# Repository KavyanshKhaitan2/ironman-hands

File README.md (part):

# Ironman-Hands!
[View in OnShape](https://cad.onshape.com/documents/6b24d13ccce8b20dadd52a3a/w/196c8f17dbb1cb6e287c322c/e/852bd395ec118001130bafdd?renderMode=0&uiState=6a15cbbf1f6b6ce009f7e8d0)

A glove which you can wear and control your computer by moving your hand and using gestures!! (It has a lot of sensors to do this!)

I will be stitching all the parts together on a glove, and then adding some more cloth on top so no exposed wires or PCBs are visible!

## Contents
Quickly jump to different parts of the README using this section!
1. [Why?](#why)
1. [Fallout Zine](#fallout-zine)
2. [PCB](#pcb)
3. [Schematics](#schematics)
4. [Case](#case)
5. [Bill of Materials](#bom)
6. [Assembly](#assembly)
## Why?
I watched the Iron Man Movie, and it was always fascinating to me how he controlled the screen using just his hands, so I decided to build to make that true and real!

## Fallout Zine
[Jump to Contents](#contents)

<image height="400" src="https://github.com/KavyanshKhaitan2/ironman-hands/blob/main/zine/Zine_PNG.png?raw=true">

- [ [Download JPEG file](https://github.com/KavyanshKhaitan2/ironman-hands/blob/main/zine/Zine_JPEG.jpg) ]
- [ [Download PNG file](https://github.com/KavyanshKhaitan2/ironman-hands/blob/main/zine/Zine_PNG.png) ]
- [ [Download High-Res PNG file](https://github.com/KavyanshKhaitan2/ironman-hands/blob/main/zine/Zine_PNG_HighRes.png) ]
- [ [Download Digital RGB PDF file](https://github.com/KavyanshKhaitan2/ironman-hands/blob/main/zine/Zine_Digital_RGB.pdf) ]
- [ [Download Print CMYK PDF file](https://github.com/KavyanshKhaitan2/ironman-hands/blob/main/zine/Zine_Print_CMYK.pdf) ]

[Jump to Contents](#contents)

## PCB
[Jump to Contents](#contents)

- [Mainboard](#mainboard)
- [Finger module](#finger-module)
- [BackLEDs](#backleds)
- [Power module](#power-module)

### Mainboard

- [ [Open in KiCanvas](https://kicanvas.org/?repo=https%3A%2F%2Fgithub.com%2FKavyanshKhaitan2%2Fironman-hands%2Fblob%2Fmain%2Fpcb%2Fmainboard.kicad_pcb) ]

[Jump to Contents](#contents)

### Finger module

- [ [Open in KiCanvas](https://kicanvas.org/?repo=https%3A%2F%2Fgithub.com%2FKavyanshKhaitan2%2Fironman-hands%2Fblob%2Fmain%2Fpcb%2Ffinger-mods.kicad_pcb) ]

[Jump to Contents](#contents)

### BackLEDs

- [ [Open in KiCanvas](https://kicanvas.org/?repo=https%3A%2F%2Fgithub.com%2FKavyanshKhaitan2%2Fironman-hands%2Fblob%2Fmain%2Fpcb%2Fbackleds.kicad_pcb) ]

[Jump to Contents](#contents)

### Power module

- [ [Open in KiCanvas](https://kicanvas.org/?repo=https%3A%2F%2Fgithub.com%2FKavyanshKhaitan2%2Fironman-hands%2Fblob%2Fmain%2Fpcb%2Fbattery_module%2Fbattery_module%2Fbattery_module.kicad_pcb) ]

[Jump to Contents](#contents)

## Schematics
[Jump to Contents](#contents)

- [Mainboard](#mainboard-1)
- [Finger module P1](#finger-module-p1)
- [Finger module P2](#finger-module-p2)
- [Power module](#power-module-1)

### Mainboard

[ [View in KiCanvas](https://kicanvas.org/?repo=https%3A%2F%2Fgithub.com%2FKavyanshKhaitan2%2Fironman-hands%2Fblob%2Fmain%2Fpcb%2Fmainboard.kicad_sch) ]

[Jump to Contents](#contents)

### Finger module P1

[ [View in KiCanvas](https://kicanvas.org/?repo=https%3A%2F%2Fgithub.com%2FKavyanshKhaitan2%2Fironman-hands%2Fblob%2Fmain%2Fpcb%2Ffinger-mods.kicad_sch) ]

[Jump to Contents](#contents)

### Finger module P2

[ [View in KiCanvas](https://kicanvas.org/?repo=https%3A%2F%2Fgithub.com%2FKavyanshKhaitan2%2Fironman-hands%2Fblob%2Fmain%2Fpcb%2Ffinger_mod_p2.kicad_sch) ]

[Jump to Contents](#contents)

### Power module

[ [View in KiCanvas](https://kicanvas.org/?repo=https%3A%2F%2Fgithub.com%2FKavyanshKhaitan2%2Fironman-hands%2Fblob%2Fmain%2Fpcb%2Fbattery_module%2Fbattery_module%2Fbattery_module.kicad_sch) ]

[Jump to Contents](#contents)

## Case
### Final assembly:

[ [View in OnShape](https://cad.onshape.com/documents/6b24d13ccce8b20dadd52a3a/w/196c8f17dbb1cb6e287c322c/e/852bd395ec118001130bafdd?renderMode=0&uiState=6a15cbbf1f6b6ce009f7e8d0) ]

[Jump to Contents](#contents)

## BOM
(Bill of Materials)

[ [View in Google Sheets](https://docs.google.com/spreadsheets/d/10JJsmnbrsMaL60rsXx-CBmIgtjZ1htyX9JACOBp3yb4/edit?usp=sharing) ]
[ [Open CSV in GitHub](https://github.com/KavyanshKhaitan2/ironman-hands/blob/main/production/BOM.csv) ]

- [Cumulative](#cumulative)
- [Mainboard](#mainboard)
- [Per-finger module](#per-finger-module)
- [Power](#power)
- [Misc](#misc)

[Jump to Contents](#contents)

### Cumulative

[Jump to Contents](#contents)

### Mainboard
<table cellspacing="0" cellpadding="0">
    <tr>
        <th>
            <div>2</div>
        </th>
        <td>PCB</td>
        <td>0.4000</td>
        <td>
            <span>USD</span>
        </td>
        <td>-</td>
        <td>5</td>
        <td>1</td>
        <td>2.00</td>
        <td>USD</td>
        <td>₹191.36</td>
        <td>$2.00</td>
    </tr>
    <tr>
        <th>
            <div>3</div>
        </th>
        <td>Header pins (90deg)</td>
        <td>0.2000</td>
        <td>
            <span>INR</span>
        </td>
        <td>
            <a href="https://quartzcomponents.com/collections/all/products/male-90-degree-pin-header-connector"
                >QuartzComponents</a
            >
        </td>
        <td>40</td>
        <td>34</td>
        <td>8.00</td>
        <td>INR</td>
        <td>₹199.36</td>
        <td>$2.08</td>
    </tr>
    <tr>
        <th>
            <div>4</div>
        </th>
        <td>TYPE-C-31-M-12</td>
        <td>0.1719</td>
        <td>
            <span>USD</span>
        </td>
        <td>
            <a href="https://www.lcsc.com/product-detail/C165948.html">LCSC</a>
        </td>
        <td>5</td>
        <td>1</td>
        <td>0.86</td>
        <td>USD</td>
        <td>₹281.60</td>
        <td>$2.94</td>
    </tr>
    <tr>
        <th>
            <div>5</div>
        </th>
        <td>LM1117MP-3.3/TR</td>
        <td>0.0931</td>
        <td>
            <span>USD</span>
        </td>
        <td>
            <a href="https://www.lcsc.com/product-detail/C498153.html">LCSC</a>
        </td>
        <td>5</td>
        <td>1</td>
        <td>0.47</td>
        <td>USD</td>
        <td>₹326.14</td>
        <td>$3.41</td>
    </tr>
    <tr>
        <th>
            <div>6</div>
        </th>
        <td>SS56 Diode</td>
        <td>0.0471</td>
        <td>
            <span>USD</span>
        </td>
        <td>
            <a href="https://www.lcsc.com/product-detail/C65009.html">LCSC</a>
        </td>
        <td>10</td>
        <td>1</td>
        <td>0.47</td>
        <td>USD</td>
        <td>₹371.21</td>
        <td>$3.88</td>
    </tr>
    <tr>
        <th>
            <div>7</div>
        </th>
        <td>ESP32-S3-WROOM-1</td>
        <td>371.0000</td>
        <td>
            <span>INR</span>
        </td>
        <td>
            <a href="https://www.etstore.in/products/a2724">ETStore</a>
        </td>
        <td>1</td>
        <td>1</td>
        <td>371.00</td>
        <td>INR</td>
        <td>₹742.21</td>
        <td>$7.76</td>
    </tr>
    <tr>
        <th>
            <div>8</div>
        </th>
        <td>LSM6DS3TR-C</td>
        <td>1.5474</td>
        <td>
            <span>USD</span>
        </td>
        <td>
            <a href="https://www.lcsc.com/product-detail/C967633.html">LCSC</a>
        </td>
        <td>1</td>
        <td>1</td>
        <td>1.55</td>
        <td>USD</td>
        <td>₹890.27</td>
        <td>$9.30</td>
    </tr>
    <tr>
        <th>
            <div>9</div>
        </th>
        <td>TCA9548APWR</td>
        <td>0.6418</td>
        <td>
            <span>USD</span>
        </td>
        <td>
            <a href="https://www.lcsc.com/product-detail/C130026.html">LCSC</a>
        </td>
        <td>1</td>
        <td>1</td>
        <td>0.64</td>
        <td>USD</td>
        <td>₹951.68</td>
        <td>$9.95</td>
    </tr>
    <tr>
        <th>
            <div>10</div>
        </th>
        <td>SK6812MINI-E</td>
        <td>0.0870</td>
        <td>
            <span>USD</span>
        </td>
        <td>
            <a href="https://www.lcsc.com/product-detail/C5149201.html">LCSC</a>
        </td>
        <td>5</td>
        <td>6</td>
        <td>0.87</td>
        <td>USD</td>
        <td>₹1,034.92</td>
        <td>$10.82</td>
    </tr>
    <tr>
        <th>
            <div>11</div>
        </th>
        <td>10k 1206 resistor</td>
        <td>0.4500</td>
        <td>
            <span>INR</span>
        </td>
        <td>
            <a
                href="https://quartzcomponents.com/collections/all/products/yageo-510k-ohm-1206-package-1-4w-smd-resistor-1-tolerance-pack-of-20-pieces"
                >QuartzComponents</a
            >
        </td>
        <td>20</td>
        <td>2</td>
        <td>9.00</td>
        <td>INR</td>
        <td>₹1,043.92</td>
        <td>$10.91</td>
    </tr>
    <tr>
        <th>
            <div>12</div>
        </th>
        <td>100nF 0805 capacitor</td>
        <td>1.5000</td>
        <td>
            <span>INR</span>
        </td>
        <td>
            <a
                href="https://quartzcomponents.com/collections/all/products/100nf-0-1uf-104-50v-1206-smd-capacitor-pack-of-10-pieces"
                >QuartzComponents</a
            >
        </td>
        <td>10</td>
        <td>2</td>
        <td>15.00</td>
        <td>INR</td>
        <td>₹1,058.92</td>
        <td>$11.07</td>
    </tr>
</table>

[Jump to Contents](#contents)

### Per-finger module
<table cellspacing="0" cellpadding="0">
    <tbody>
        <tr>
            <td>Item Name</td>
            <td>
                <div>Unit Price</div>
            </td>
            <td>
                <div>Cur.</div>
            </td>
            <td>Link</td>
            <td>
                <div>Min Qty.</div>
            </td>
            <td>
                <div>Qty.</div>
            </td>
            <td>
                <div>Amount</div>
            </td>
            <td>Co1</td>
            <td>
                <div>1.. Run. Total</div>
            </td>
            <td>
                <div>2.. Run. Total</div>
            </td>
        </tr>
        <tr>
            <td>PCB</td>
            <td>0.4000</td>
            <td>
                <span>USD</span>
            </td>
            <td>-</td>
            <td>5</td>
            <td>4</td>
            <td>2.00</td>
            <td>USD</td>
            <td>₹191.36</td>
            <td>$2.00</td>
        </tr>
        <tr>
            <td>Header pins (90deg)</td>
            <td>0.2000</td>
            <td>
                <span>INR</span>
            </td>
            <td>
                <a href="https://quartzcomponents.com/collections/all/products/male-90-degree-pin-header-connector"
                    >QuartzComponents</a
                >
            </td>
            <td>40</td>
            <td>18</td>
            <td>8.00</td>
            <td>INR</td>
            <td>₹199.36</td>
            <td>$2.08</td>
        </tr>
        <tr>
            <td>LSM6DS3TR-C</td>
            <td>1.5474</td>
            <td>
                <span>USD</span>
            </td>
            <td>
                <a href="https://www.lcsc.com/product-detail/C967633.html">LCSC</a>
            </td>
            <td>1</td>
            <td>2</td>
            <td>3.09</td>
            <td>USD</td>
            <td>₹495.48</td>
            <td>$5.18</td>
        </tr>
        <tr>
            <td>10k 1206 resistor</td>
            <td>0.4500</td>
            <td>
                <span>INR</span>
            </td>
            <td>
                <a
                    href="https://quartzcomponents.com/collections/all/products/yageo-510k-ohm-1206-package-1-4w-smd-resistor-1-tolerance-pack-of-20-pieces"
                    >QuartzComponents</a
                >
            </td>
            <td>40</td>
            <td>4</td>
            <td>18.00</td>
            <td>INR</td>
            <td>₹513.48</td>
            <td>$5.37</td>
        </tr>
        <tr>
            <td>100nF 0805 capacitor</td>
            <td>1.5000</td>
            <td>
                <span>INR</span>
            </td>
            <td>
                <a
                    href="https://quartzcomponents.com/collections/all/products/100nf-0-1uf-104-50v-1206-smd-capacitor-pack-of-10-pieces"
                    >QuartzComponents</a
                >
            </td>
            <td>30</td>
            <td>4</td>
            <td>45.00</td>
            <td>INR</td>
            <td>₹558.48</td>
            <td>$5.84</td>
        </tr>
        <tr>
            <td>SK6812MINI-E</td>
            <td>0.0870</td>
            <td>
                <span>USD</span>
            </td>
            <td>
                <a href="https://www.lcsc.com/product-detail/C5149201.html">LCSC</a>
            </td>
            <td>5</td>
            <td>2</td>
            <td>0.44</td>
            <td>USD</td>
            <td>₹600.10</td>
            <td>$6.27</td>
        </tr>
    </tbody>
</table>

[Jump to Contents](#contents)

### Power

<table cellspacing="0" cellpadding="0">
    <tr>
        <td>Item Name</td>
        <td>Unit Price</td>
        <td>Cur.</td>
        <td>Link</td>
        <td>Min Qty.</td>
        <td>Qty.</td>
        <td>Amount</td>
        <td>Co1</td>
        <td>1.. Run. Total</td>
        <td>2.. Run. Total</td>
    </tr>
    <tr>
        <td>PCB</td>
        <td>1.4000</td>
        <td>USD</td>
        <td>-</td>
        <td>5</td>
        <td>1</td>
        <td>7.00</td>
        <td>USD</td>
        <td>₹669.78</td>
        <td>$7.00</td>
    </tr>
    <tr>
        <td>Header pins (90deg)</td>
        <td>0.2000</td>
        <td>INR</td>
        <td>
            <a href="https://quartzcomponents.com/collections/all/products/male-90-degree-pin-header-connector"
                >QuartzComponents</a
            >
        </td>
        <td>40</td>
        <td>16</td>
        <td>8.00</td>
        <td>INR</td>
        <td>₹8.00</td>
        <td>$0.08</td>
    </tr>
    <tr>
        <td>DC Barrel Jack</td>
        <td>6.0000</td>
        <td>INR</td>
        <td>
            <a href="https://quartzcomponents.com/products/female-dc-power-supply-connector-barrel-dc-jack"
                >QuartzComponents</a
            >
        </td>
        <td>1</td>
        <td>1</td>
        <td>6.00</td>
        <td>INR</td>
        <td>₹14.00</td>
        <td>$0.15</td>
    </tr>
    <tr>
        <td>DC Power Adapter</td>
        <td>132.0000</td>
        <td>
            <span>INR</span>
        </td>
        <td>
            <a href="https://quartzcomponents.com/products/12v-1a-dc-power-adapter">QuartzComponents</a>
        </td>
        <td>1</td>
        <td>1</td>
        <td>132.00</td>
        <td>INR</td>
        <td>₹146.00</td>
        <td>$1.53</td>
    </tr>
    <tr>
        <td>SPST Power Switch</td>
        <td>6.0000</td>
        <td>
            <span>INR</span>
        </td>
        <td>
            <a href="https://www.etstore.in/products/b8017">ETStore</a>
        </td>
        <td>2</td>
        <td>1</td>
        <td>12.00</td>
        <td>INR</td>
        <td>₹158.00</td>
        <td>$1.65</td>
    </tr>
    <tr>
        <td>TP5100 module</td>
        <td>57.0000</td>
        <td>
            <span>INR</span>
        </td>
        <td>
            <a
                href="https://quartzcomponents.com/collections/all/products/tp5100-4-2v-8-4v-li-ion-battery-charging-module"
                >QuartzComponents</a
            >
        </td>
        <td>1</td>
        <td>1</td>
        <td>57.00</td>
        <td>INR</td>
        <td>₹215.00</td>
        <td>$2.25</td>
    </tr>
    <tr>
        <td>TPS54302DDCR</td>
        <td>0.3140</td>
        <td>
            <span>USD</span>
        </td>
        <td>
            <a href="https://www.lcsc.com/product-detail/C311983.html">LCSC</a>
        </td>
        <td>5</td>
        <td>2</td>
        <td>1.57</td>
        <td>USD</td>
        <td>₹365.22</td>
        <td>$3.82</td>
    </tr>
    <tr>
        <td>22uF|3.55mOhm Cap</td>
        <td>0.0904</td>
        <td>
            <span>USD</span>
        </td>
        <td>
            <a href="https://www.lcsc.com/product-detail/C5677683.html">LCSC</a>
        </td>
        <td>5</td>
        <td>1</td>
        <td>0.45</td>
        <td>USD</td>
        <td>₹408.47</td>
        <td>$4.27</td>
    </tr>
    <tr>
        <td>100nF|280mOhm Cap</td>
        <td>0.0067</td>
        <td>
            <span>USD</span>
        </td>
        <td>
            <a href="https://www.lcsc.com/product-detail/C519980.html">LCSC</a>
        </td>
        <td>100</td>
        <td>2</td>
        <td>0.67</td>
        <td>USD</td>
        <td>₹472.58</td>
        <td>$4.94</td>
    </tr>
    <tr>
        <td>5uH|22mOhm Induc</td>
        <td>0.5559</td>
        <td>USD</td>
        <td>
            <a href="https://www.lcsc.com/product-detail/C780188.html">LCSC</a>
        </td>
        <td>2</td>
        <td>2</td>
        <td>1.11</td>
        <td>USD</td>
        <td>₹578.96</td>
        <td>$6.05</td>
    </tr>
    <tr>
        <td>47pF Cap</td>
        <td>1.3000</td>
        <td>INR</td>
        <td>
            <a
                href="https://quartzcomponents.com/collections/all/products/kemet-47pf-50v-805-smd-pack-c0g-multilayer-ceramic-capacitor-5-tolerence-pack-of-20"
                >QuartzComponents</a
            >
        </td>
        <td>20</td>
        <td>1</td>
        <td>26.00</td>
        <td>INR</td>
        <td>₹604.96</td>
        <td>$6.32</td>
    </tr>
    <tr>
        <td>100k 1206 resistor</td>
        <td>0.4500</td>
        <td>
            <span>INR</span>
        </td>
        <td>
            <a
                href="https://quartzcomponents.com/products/yageo-100k-ohm-1206-package-1-4w-smd-resistor-1-tolerance-pack-of-20-pieces"
                >QuartzComponents</a
            >
        </td>
        <td>20</td>
        <td>2</td>
        <td>9.00</td>
        <td>INR</td>
        <td>₹613.96</td>
        <td>$6.42</td>
    </tr>
    <tr>
        <td>13.7k 1206 resistor</td>
        <td>0.0059</td>
        <td>
            <span>USD</span>
        </td>
        <td>
            <a href="https://www.lcsc.com/product-detail/C2903322.html">LCSC</a>
        </td>
        <td>50</td>
        <td>1</td>
        <td>0.30</td>
        <td>USD</td>
        <td>₹642.18</td>
        <td>$6.71</td>
    </tr>
    <tr>
        <td>47uF 1210 capacitor</td>
        <td>0.1754</td>
        <td>
            <span>USD</span>
        </td>
        <td>
            <a href="https://www.lcsc.com/product-detail/C77101.html">LCSC</a>
        </td>
        <td>5</td>
        <td>3</td>
        <td>0.88</td>
        <td>USD</td>
        <td>₹726.10</td>
        <td>$7.59</td>
    </tr>
    <tr>
        <td>10uF 0805 capacitor</td>
        <td>0.0317</td>
        <td>
            <span>USD</span>
        </td>
        <td>
            <a href="https://www.lcsc.com/product-detail/C5677680.html">LCSC</a>
        </td>
        <td>20</td>
        <td>2</td>
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
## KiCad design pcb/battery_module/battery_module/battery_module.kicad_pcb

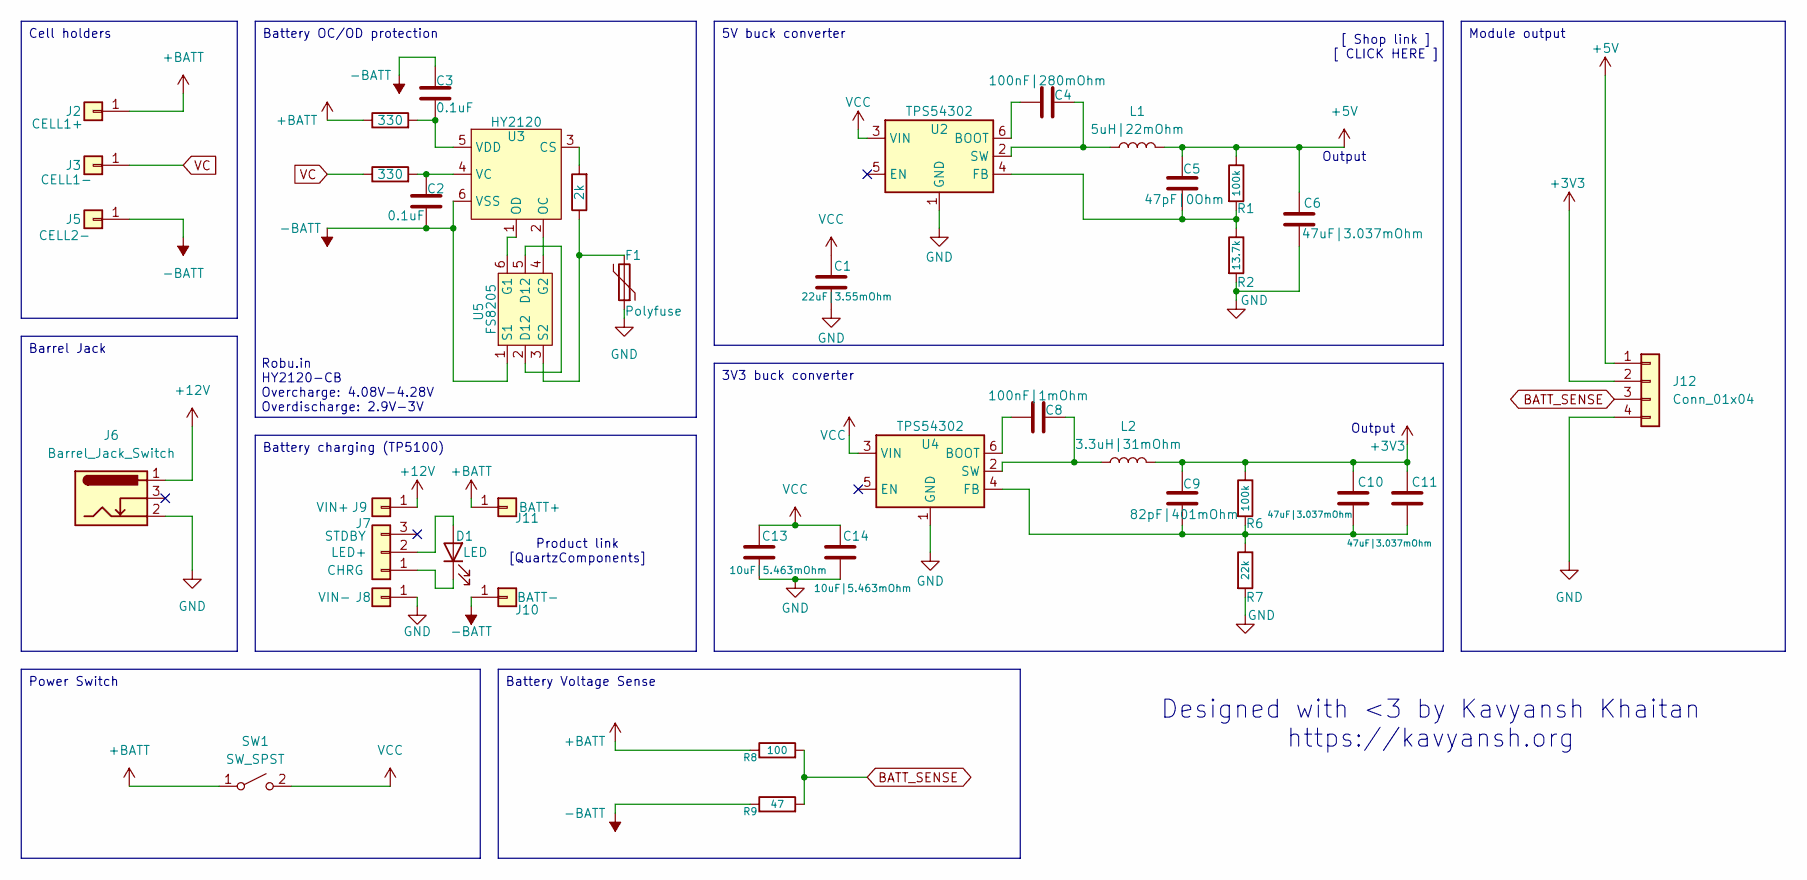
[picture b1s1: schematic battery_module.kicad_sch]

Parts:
C1: 22uF|3.55mOhm; C_0805_2012Metric_Pad1.18x1.45mm_HandSolder
C2, C3: 0.1uF; C_1206_3216Metric_Pad1.33x1.80mm_HandSolder
C4: 100nF|280mOhm; C_0805_2012Metric_Pad1.18x1.45mm_HandSolder
C5: 47pF|0Ohm; C_0805_2012Metric_Pad1.18x1.45mm_HandSolder
C6, C10, C11: 47uF|3.037mOhm; C_1210_3225Metric_Pad1.33x2.70mm_HandSolder
C8: 100nF|1mOhm; C_0805_2012Metric_Pad1.18x1.45mm_HandSolder
C9: 82pF|401mOhm; C_0805_2012Metric_Pad1.18x1.45mm_HandSolder
C13, C14: 10uF|5.463mOhm; C_0805_2012Metric_Pad1.18x1.45mm_HandSolder
D1: LED; LED_D2.0mm_W4.0mm_H2.8mm_FlatTop
F1: Polyfuse; Fuse_Littelfuse_395Series
J2: CELL1+; PinSocket_1x01_P2.54mm_Vertical
J3: CELL1-; PinSocket_1x01_P2.54mm_Vertical
J5: CELL2-; PinSocket_1x01_P2.54mm_Vertical
J6: Barrel_Jack_Switch; BarrelJack_Horizontal
J7: Conn_01x03; PinHeader_1x03_P2.00mm_Vertical
J8, J9, J10, J11: Conn_01x01; PinHeader_1x01_P2.54mm_Vertical
J12: Conn_01x04; PinSocket_1x04_P2.54mm_Vertical
L1: 5uH|22mOhm; L_APV_ANR8040
L2: 3.3uH|31mOhm; L_Bourns-SRN8040_8x8.15mm
R1, R6: 100k; R_1206_3216Metric_Pad1.30x1.75mm_HandSolder
R2: 13.7k; R_1206_3216Metric_Pad1.30x1.75mm_HandSolder
R4, R11: 330; R_1206_3216Metric_Pad1.30x1.75mm_HandSolder
R5: 2k; R_1206_3216Metric_Pad1.30x1.75mm_HandSolder
R7: 22k; R_1206_3216Metric_Pad1.30x1.75mm_HandSolder
R8: 100; R_Axial_DIN0207_L6.3mm_D2.5mm_P15.24mm_Horizontal
R9: 47; R_Axial_DIN0207_L6.3mm_D2.5mm_P15.24mm_Horizontal
SW1: SW_SPST; PinSocket_1x02_P2.54mm_Vertical
U2: TPS54302; SOT-23-6_Handsoldering
U3: HY2120; SOT-23-6_Handsoldering
U4: TPS54302; SOT-23-6
U5: FS8205; SOT-23-6_Handsoldering

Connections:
+3V3: C9.1, C10.1, C11.1, J12.2, L2.2, R6.1
+5V: C5.1, C6.1, J12.1, L1.2, R1.1
+12V: J6.1, J9.1 (Pin_1_1)
+BATT: J2.1 (Pin_1_1), J11.1 (Pin_1_1), R4.1, R8.1, SW1.1 (A)
-BATT: C2.2, C3.1, J5.1 (Pin_1_1), J10.1 (Pin_1_1), R9.1, U3.6 (VSS), U5.1 (S1)
BATT_SENSE: J12.3, R8.2, R9.2
GND: C1.2, C6.2, C13.2, C14.2, F1.1, J6.2, J8.1 (Pin_1_1), J12.4, R2.2, R7.2, U2.1 (GND), U4.1 (GND)
unnamed: D1.2 (A), J7.2
unnamed: D1.1 (K), J7.1
unnamed: C4.1, U2.6 (BOOT)
unnamed: C5.2, R1.2, R2.1, U2.4 (FB)
unnamed: C4.2, L1.1, U2.2 (SW)
unnamed: R5.2, U3.3 (CS)
unnamed: U3.2 (OC), U5.4 (G2)
unnamed: U3.1 (OD), U5.6 (G1)
unnamed: C2.1, R11.2, U3.4 (VC)
unnamed: C3.2, R4.2, U3.5 (VDD)
unnamed: C8.1, U4.6 (BOOT)
unnamed: C9.2, C10.2, C11.2, R6.2, R7.1, U4.4 (FB)
unnamed: C8.2, L2.1, U4.2 (SW)
unnamed: U5.2 (D12), U5.5 (D12)
unnamed: F1.2, R5.1, U5.3 (S2)
VC: J3.1 (Pin_1_1), R11.1
VCC: C1.1, C13.1, C14.1, SW1.2 (B), U2.3 (VIN), U4.3 (VIN)

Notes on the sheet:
Output
Product link [QuartzComponents]
[ Shop link ] [ CLICK HERE ]
Designed with <3 by Kavyansh Khaitan https://kavyansh.org
Robu.in HY2120-CB Overcharge: 4.08V-4.28V Overdischarge: 2.9V-3V
Cell holders
Module output
Power Switch
Battery charging (TP5100)
Battery Voltage Sense
3V3 buck converter
Battery OC/OD protection
5V buck converter
Barrel Jack

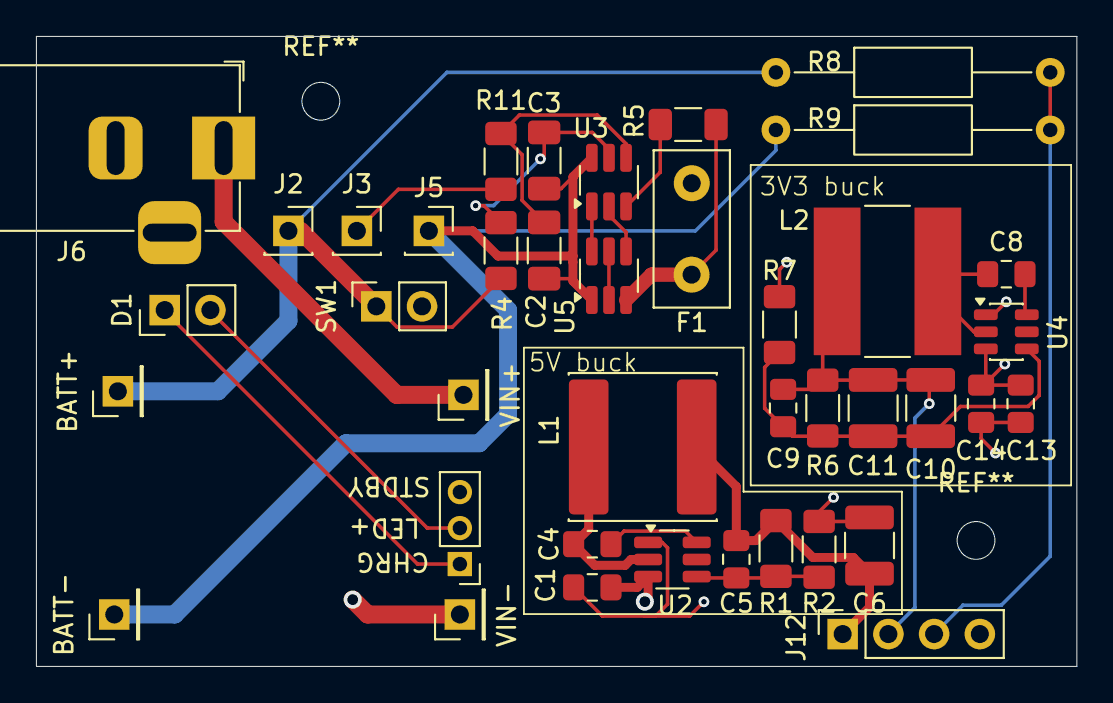
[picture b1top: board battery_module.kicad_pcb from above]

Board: 4 copper layers, 57.8 x 35.0 mm, 40 parts (0 on the bottom side), 24 nets.

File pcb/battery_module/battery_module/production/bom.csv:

Designator,Footprint,Quantity,Value,LCSC Part #
C1,0805,1,22uF|3.55mOhm,
"C10, C11, C6",1210,3,47uF|3.037mOhm,
"C13, C14",0805,2,10uF|5.463mOhm,
"C2, C3",1206,2,0.1uF,
C4,0805,1,100nF|280mOhm,
C5,0805,1,47pF|0Ohm,
C8,0805,1,100nF|1mOhm,
C9,0805,1,82pF|401mOhm,
D1,PinHeader_1x02_P2.54mm_Vertical,1,LED,
F1,Fuse_Littelfuse_395Series,1,Polyfuse,
"J10, J11, J8, J9",PinHeader_1x01_P2.54mm_Vertical,4,Conn_01x01,
J12,PinSocket_1x04_P2.54mm_Vertical,1,Conn_01x04,
J2,PinSocket_1x01_P2.54mm_Vertical,1,CELL1+,
J3,PinSocket_1x01_P2.54mm_Vertical,1,CELL1-,
J5,PinSocket_1x01_P2.54mm_Vertical,1,CELL2-,
J6,BarrelJack_Horizontal,1,Barrel_Jack_Switch,
J7,PinHeader_1x03_P2.00mm_Vertical,1,Conn_01x03,
L1,L_APV_ANR8040,1,5uH|22mOhm,
L2,L_Bourns-SRN8040_8x8.15mm,1,3.3uH|31mOhm,
"R1, R6",1206,2,100k,
"R11, R4",1206,2,330,
R2,1206,1,13.7k,
R5,1206,1,2k,
R7,1206,1,22k,
R8,R_Axial_DIN0207_L6.3mm_D2.5mm_P15.24mm_Horizontal,1,100,
R9,R_Axial_DIN0207_L6.3mm_D2.5mm_P15.24mm_Horizontal,1,47,
SW1,PinSocket_1x02_P2.54mm_Vertical,1,SW_SPST,
U2,SOT-23-6_Handsoldering,1,TPS54302,
U3,SOT-23-6_Handsoldering,1,HY2120,
U4,SOT-23-6,1,TPS54302,
U5,SOT-23-6_Handsoldering,1,FS8205,

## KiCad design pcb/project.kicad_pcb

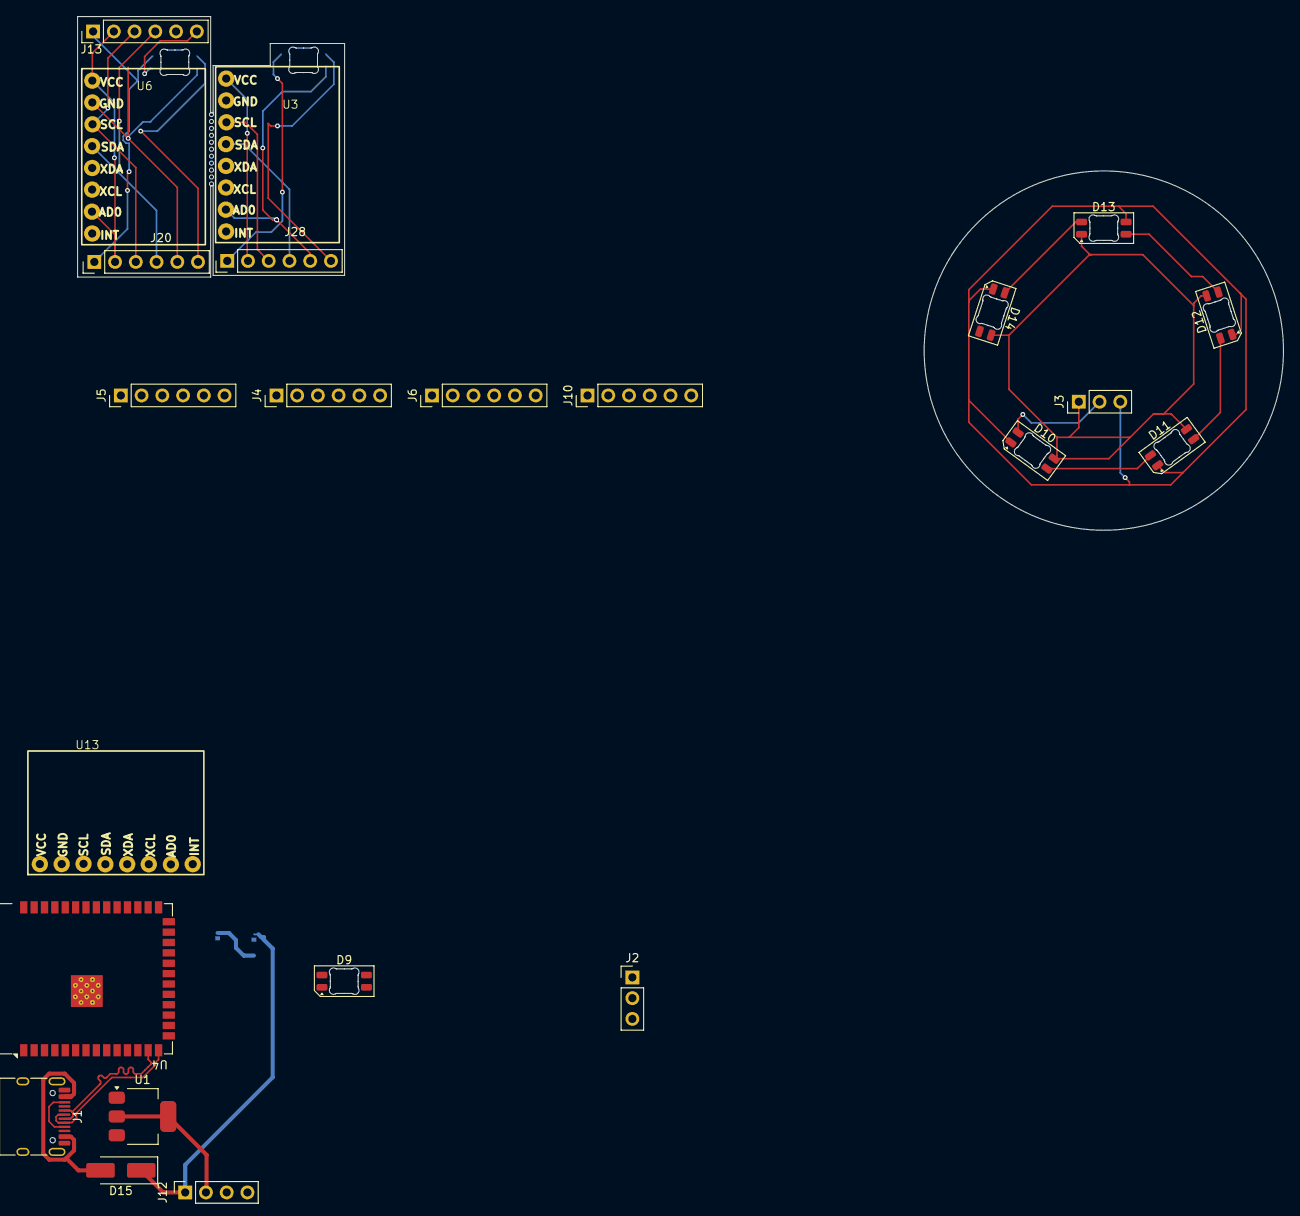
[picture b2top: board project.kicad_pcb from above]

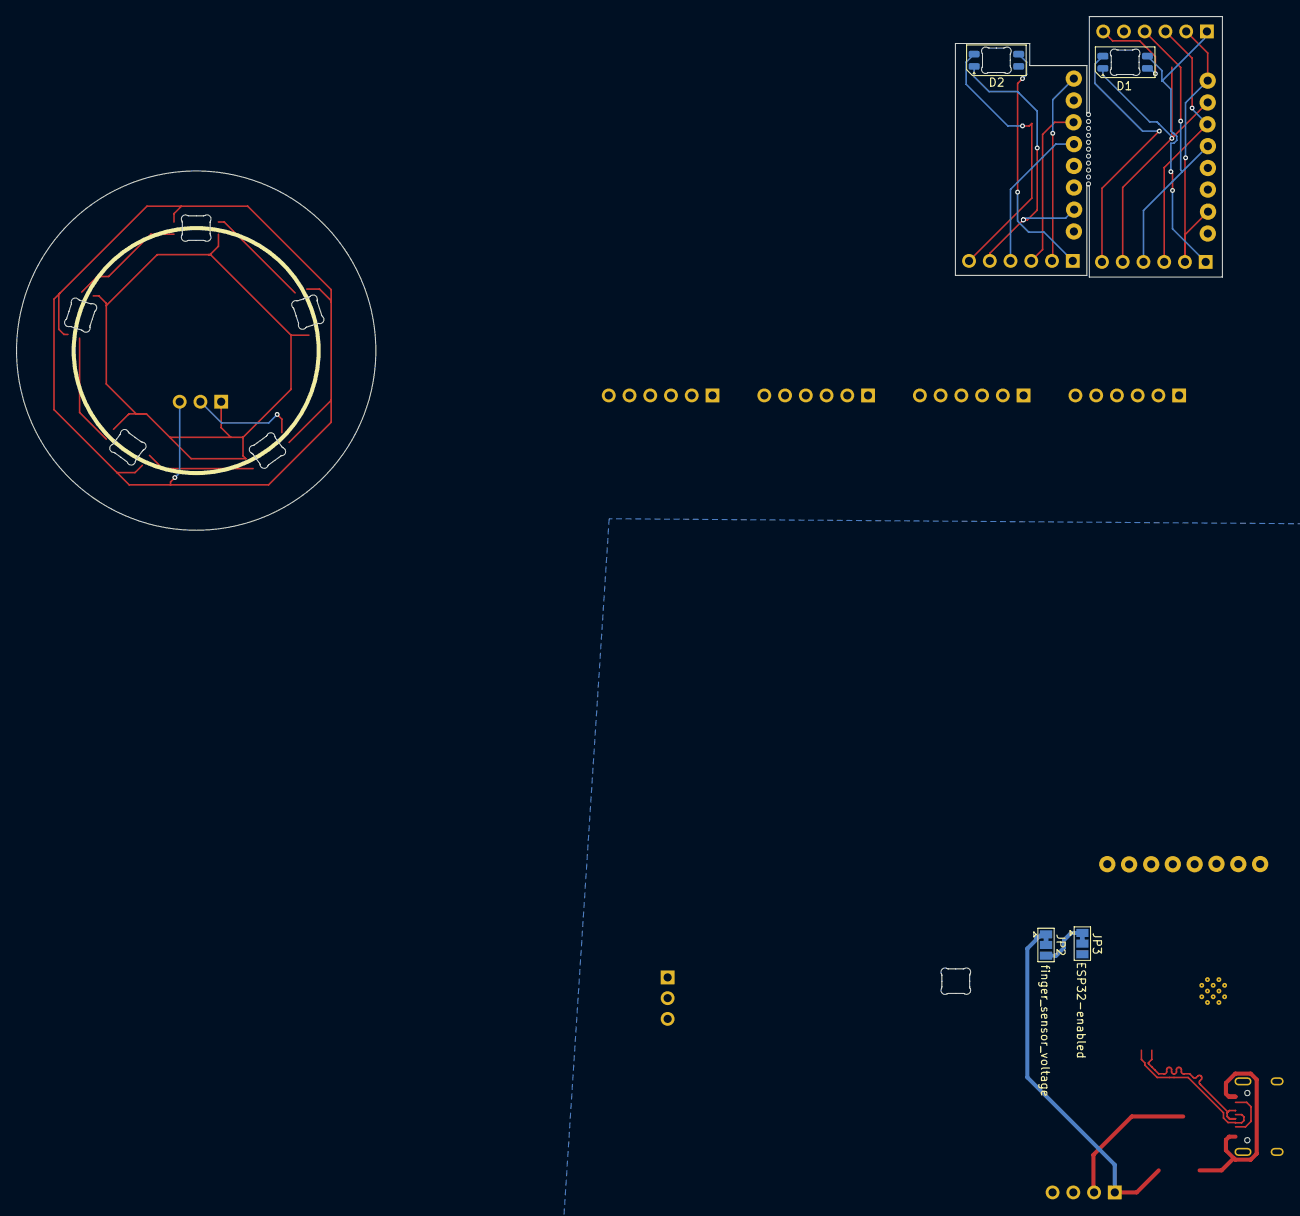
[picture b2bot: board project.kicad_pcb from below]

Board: 2 copper layers, 147.7 x 119.7 mm, 27 parts (4 on the bottom side), 45 nets.

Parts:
D1, D2, D9, D10, D11, D12, D13, D14: SK6812MINI-E; LED_SK6812MINI-E_3.2x2.8mm_P1.5mm_ReverseMount
D15: D; D_SMA_Handsoldering
J1: USB_C_Receptacle_USB2.0_14P; USB_C_Receptacle_HRO_TYPE-C-31-M-12
J2, J3: Conn_01x03; PinHeader_1x03_P2.54mm_Vertical
J4, J5, J6, J10, J13, J20, J28: Conn_01x06; PinHeader_1x06_P2.54mm_Vertical
J12: Conn_01x04; PinSocket_1x04_P2.54mm_Vertical
JP2: finger_sensor_voltage; SolderJumper-3_P1.3mm_Bridged12_Pad1.0x1.5mm
JP3: ESP32-enabled; SolderJumper-3_P1.3mm_Bridged12_Pad1.0x1.5mm
U1: LM1117MP-3.3; SOT-223-3_TabPin2
U3, U6, U13: GY-521; MPU-6050
U4: ESP32-S3-WROOM-1

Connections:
+3V3: J12.2, JP2.3 (B), JP3.1 (A), U1.2 (VO), U4.2 (3V3)
+5V: D9.3 (VDD), D15.1 (K), J2.1, J4.1, J5.1, J6.1, J10.1, J12.1, JP2.1 (A)
BATT_SENSE: J12.3, U4.8 (IO15)
GND: D9.1 (VSS), J1.A1 (GND), J1.A12 (GND), J1.B1 (GND), J1.B12 (GND), J1.SH (SHIELD), J2.3, J4.5, J5.5, J6.5, J10.5, J12.4, JP3.3 (B), U1.1 (GND), U4.1 (GND), U4.40 (GND), U4.41 (GND), U13.2 (GND)
LED0: D9.2 (DIN), U4.27 (IO0)
LED1: J4.6, U4.39 (IO1)
LED2: J5.6, U4.38 (IO2)
LED3: J6.6, U4.15 (IO3)
LED4: J10.6, U4.4 (IO4)
unnamed: D1.2 (DIN), J20.6
unnamed: D1.4 (DOUT), J13.6
unnamed: D1.3 (VDD), J13.1, J20.1
unnamed: D1.1 (VSS), J13.5, J20.5, U6.2 (GND)
unnamed: D2.2 (DIN), J28.6
unnamed: D2.3 (VDD), J28.1
unnamed: D2.1 (VSS), J28.5, U3.2 (GND), U3.7 (AD0)
unnamed: D9.4 (DOUT), J2.2
unnamed: D10.2 (DIN), J3.2
unnamed: D10.4 (DOUT), D11.2 (DIN)
unnamed: D10.3 (VDD), D11.3 (VDD), D12.3 (VDD), D13.3 (VDD), D14.3 (VDD), J3.1
unnamed: D10.1 (VSS), D11.1 (VSS), D12.1 (VSS), D13.1 (VSS), D14.1 (VSS), J3.3
unnamed: D11.4 (DOUT), D12.2 (DIN)
unnamed: D12.4 (DOUT), D13.2 (DIN)
unnamed: D13.4 (DOUT), D14.2 (DIN)
unnamed: D15.2 (A), J1.A4 (VBUS), J1.A9 (VBUS), J1.B4 (VBUS), J1.B9 (VBUS), U1.3 (VI)
unnamed: J4.2, J5.2, J6.2, J10.2, JP2.2 (C), U13.1 (VCC), U13.7 (AD0)
unnamed: J13.2, J20.2, U6.1 (VCC), U6.7 (AD0)
unnamed: J13.3, J20.3, U6.3 (SCL)
unnamed: J13.4, J20.4, U6.4 (SDA)
unnamed: J28.2, U3.1 (VCC)
unnamed: J28.3, U3.3 (SCL)
unnamed: J28.4, U3.4 (SDA)
unnamed: JP3.2 (C), U4.3 (EN)
SC0: J4.3, U4.5 (IO5)
SC1: J5.3, U4.7 (IO7)
SC2: J6.3, U4.17 (IO9)
SC3: J10.3, U4.19 (IO11)
SC4: U4.21 (IO13), U13.3 (SCL)
SD0: J4.4, U4.6 (IO6)
SD1: J5.4, U4.12 (IO8)
SD2: J6.4, U4.18 (IO10)
SD3: J10.4, U4.20 (IO12)
SD4: U4.22 (IO14), U13.4 (SDA)
USB_D+: J1.A6 (D+), J1.B6 (D+), U4.14 (USB_D+)
USB_D-: J1.A7 (D-), J1.B7 (D-), U4.13 (USB_D-)

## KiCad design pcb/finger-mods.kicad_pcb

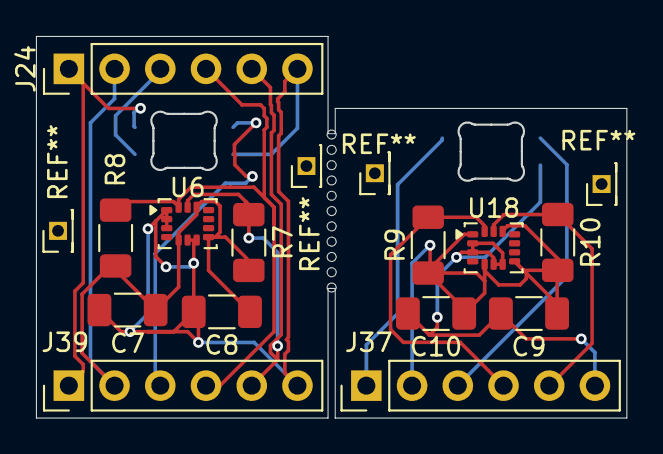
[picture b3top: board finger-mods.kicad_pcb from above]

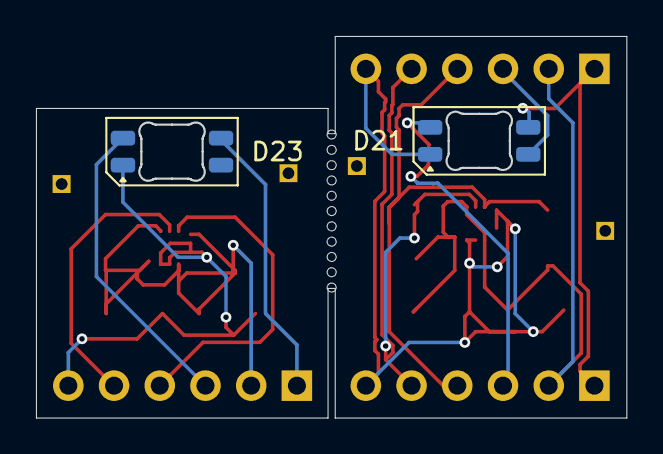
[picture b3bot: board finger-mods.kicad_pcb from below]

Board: 2 copper layers, 32.8 x 21.2 mm, 15 parts (2 on the bottom side), 10 nets.

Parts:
C7, C8, C9, C10: 100nF; C_1206_3216Metric_Pad1.33x1.80mm_HandSolder
D21, D23: SK6812MINI-E; LED_SK6812MINI-E_3.2x2.8mm_P1.5mm_ReverseMount
J24, J37, J39: Conn_01x06; PinHeader_1x06_P2.54mm_Vertical
R7, R8, R9, R10: 10k; R_1206_3216Metric_Pad1.30x1.75mm_HandSolder
U6, U18: LSM6DS3; LGA-14_3x2.5mm_P0.5mm_LayoutBorder3x4y

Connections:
+3V3: C7.1, C8.1, C9.1, C10.1, J24.2, J37.2, J39.2, R7.1, R8.1, R9.1, R10.1, U6.5 (VDDIO), U6.8 (VDD), U6.12 (CS), U18.1 (SDO/SA0), U18.5 (VDDIO), U18.8 (VDD), U18.12 (CS)
+5V: D21.3 (VDD), D23.3 (VDD), J24.1, J37.1, J39.1
/DIN: D21.2 (DIN), J39.3
/Finger Module P2/DIN: D23.2 (DIN), J37.3
/Finger Module P2/SCL: J37.5, R10.2, U18.13 (SCL)
/Finger Module P2/SDA: J37.4, R9.2, U18.14 (SDA)
/SCL: J24.5, J39.5, R7.2, U6.13 (SCL)
/SDA: J24.4, J39.4, R8.2, U6.14 (SDA)
GND: C7.2, C8.2, C9.2, C10.2, D21.1 (VSS), D23.1 (VSS), J24.6, J37.6, J39.6, U6.1 (SDO/SA0), U6.2 (SDX), U6.3 (SCX), U6.6 (GND), U6.7 (GND), U18.2 (SDX), U18.3 (SCX), U18.6 (GND), U18.7 (GND)
unnamed: D21.4 (DOUT), J24.3

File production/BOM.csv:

Item Name,Unit Price,Cur.,Link,Column 11,Min Qty.,Qty.,Amount,Co1,1.. Run. Total,2.. Run. Total
Mainboard PCB,0.4000,USD,jlcpcb.com,http://jlcpcb.com/,5,1,2.00,USD,₹191.51,$2.00
Per-finger module PCB,0.4000,USD,jlcpcb.com,http://jlcpcb.com/,5,4,2.00,USD,₹191.51,$2.00
Power module PCB,1.4000,USD,jlcpcb.com,http://jlcpcb.com/,5,1,7.00,USD,₹861.80,$9.00
Header pins (90deg),0.2000,INR,QuartzComponents,https://quartzcomponents.com/collections/all/products/male-9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,40,122,32.00,INR,₹223.51,$2.33
TYPE-C-31-M-12,0.1719,USD,LCSC,https://www.lcsc.com/product-detail/C165948.html,5,1,0.86,USD,₹305.81,$3.19
LM1117MP-3.3/TR,0.0931,USD,LCSC,https://www.lcsc.com/product-detail/C498153.html,5,1,0.47,USD,₹350.39,$3.66
SS56 Diode,0.0471,USD,LCSC,https://www.lcsc.com/product-detail/C65009.html,10,1,0.47,USD,₹395.49,$4.13
ESP32-S3-WROOM-1,371.0000,INR,ETStore,https://www.etstore.in/products/a2724,1,1,371.00,INR,₹766.49,$8.00
LSM6DS3TR-C,1.5474,USD,LCSC,https://www.lcsc.com/product-detail/C967633.html,1,9,13.93,USD,"₹2,100.04",$21.93
TCA9548APWR,0.6418,USD,LCSC,https://www.lcsc.com/product-detail/C130026.html,1,1,0.64,USD,"₹2,161.50",$22.57
SK6812MINI-E,0.0870,USD,LCSC,https://www.lcsc.com/product-detail/C5149201.html,5,14,1.31,USD,"₹2,286.46",$23.88
10k 1206 resistor,0.4500,INR,QuartzComponents,https://quartzcomponents.com/collections/all/products/yageo-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,20,2,9.00,INR,"₹2,295.46",$23.97
100nF 0805 capacitor,1.5000,INR,QuartzComponents,https://quartzcomponents.com/collections/all/products/100nf-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,10,2,15.00,INR,"₹2,310.46",$24.13
10k 1206 resistor,0.4500,INR,QuartzComponents,https://quartzcomponents.com/collections/all/products/yageo-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,40,16,18.00,INR,"₹2,328.46",$24.32
100nF 0805 capacitor,1.5000,INR,QuartzComponents,https://quartzcomponents.com/collections/all/products/100nf-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,30,16,45.00,INR,"₹2,373.46",$24.79
DC Barrel Jack,6.0000,INR,QuartzComponents,https://quartzcomponents.com/products/female-dc-power-supply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,1,1,6.00,INR,"₹2,379.46",$24.85
DC Power Adapter,132.0000,INR,QuartzComponents,https://quartzcomponents.com/products/12v-1a-dc-power-adapter,1,1,132.00,INR,"₹2,511.46",$26.23
SPST Power Switch,6.0000,INR,ETStore,https://www.etstore.in/products/b8017,2,1,12.00,INR,"₹2,523.46",$26.35
TP5100 module,57.0000,INR,QuartzComponents,https://quartzcomponents.com/collections/all/products/tp5100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,1,1,57.00,INR,"₹2,580.46",$26.95
TPS54302DDCR,0.3140,USD,LCSC,https://www.lcsc.com/product-detail/C311983.html,5,2,1.57,USD,"₹2,730.80",$28.52
22uF|3.55mOhm Cap,0.0904,USD,LCSC,https://www.lcsc.com/product-detail/C5677683.html,5,1,0.45,USD,"₹2,774.08",$28.97
100nF|280mOhm Cap,0.0067,USD,LCSC,https://www.lcsc.com/product-detail/C519980.html,100,2,0.67,USD,"₹2,838.23",$29.64
5uH|22mOhm Induc,0.5559,USD,LCSC,https://www.lcsc.com/product-detail/C780188.html,2,2,1.11,USD,"₹2,944.70",$30.75
47pF Cap,1.3000,INR,QuartzComponents,https://quartzcomponents.com/collections/all/products/kemet-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,20,1,26.00,INR,"₹2,970.70",$31.02
100k 1206 resistor,0.4500,INR,QuartzComponents,https://quartzcomponents.com/products/yageo-100k-ohm-1206-pa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,20,2,9.00,INR,"₹2,979.70",$31.12
13.7k 1206 resistor,0.0059,USD,LCSC,https://www.lcsc.com/product-detail/C2903322.html,50,1,0.30,USD,"₹3,007.94",$31.41
47uF 1210 capacitor,0.1754,USD,LCSC,https://www.lcsc.com/product-detail/C77101.html,5,3,0.88,USD,"₹3,091.92",$32.29
10uF 0805 capacitor,0.0317,USD,LCSC,https://www.lcsc.com/product-detail/C5677680.html,20,2,0.63,USD,"₹3,152.63",$32.92
3.3uH inductor,0.5559,USD,LCSC,https://www.lcsc.com/product-detail/C780188.html,2,2,1.11,USD,"₹3,259.09",$34.04
82pF 0805 capacitor,0.0315,USD,LCSC,https://www.lcsc.com/product-detail/C597385.html,5,1,0.16,USD,"₹3,274.17",$34.19
22k 1206 resistor,0.4500,INR,QuartzComponents,https://quartzcomponents.com/products/yageo-22k-ohm-1206-pac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,20,1,9.00,INR,"₹3,283.17",$34.29
100 THT resistor,0.8000,INR,QuartzComponents,https://quartzcomponents.com/products/100-ohm-1-4-watt-resis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,10,1,8.00,INR,"₹3,291.17",$34.37
47 THT resistor,0.8000,INR,QuartzComponents,https://quartzcomponents.com/products/47-ohm-1-4-watt-resist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,10,1,8.00,INR,"₹3,299.17",$34.45
Gloves,499.0000,INR,Decathlon,https://www.decathlon.in/p/8543424/men-golf-resistance-glove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,1,1,499.00,INR,"₹3,798.17",$39.67
Female-to-Female Jumper Wires,1.0500,INR,QuartzComponents,https://quartzcomponents.com/collections/all/products/female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,40,55,84.00,INR,"₹3,882.17",$40.54

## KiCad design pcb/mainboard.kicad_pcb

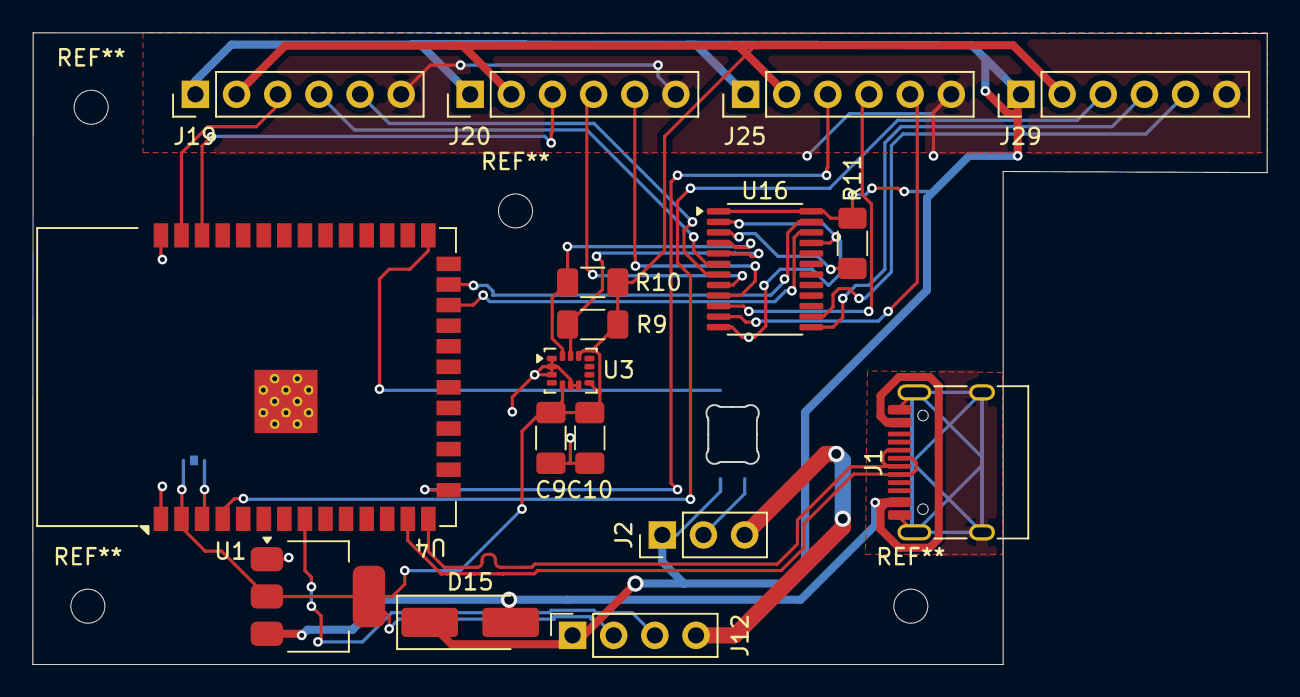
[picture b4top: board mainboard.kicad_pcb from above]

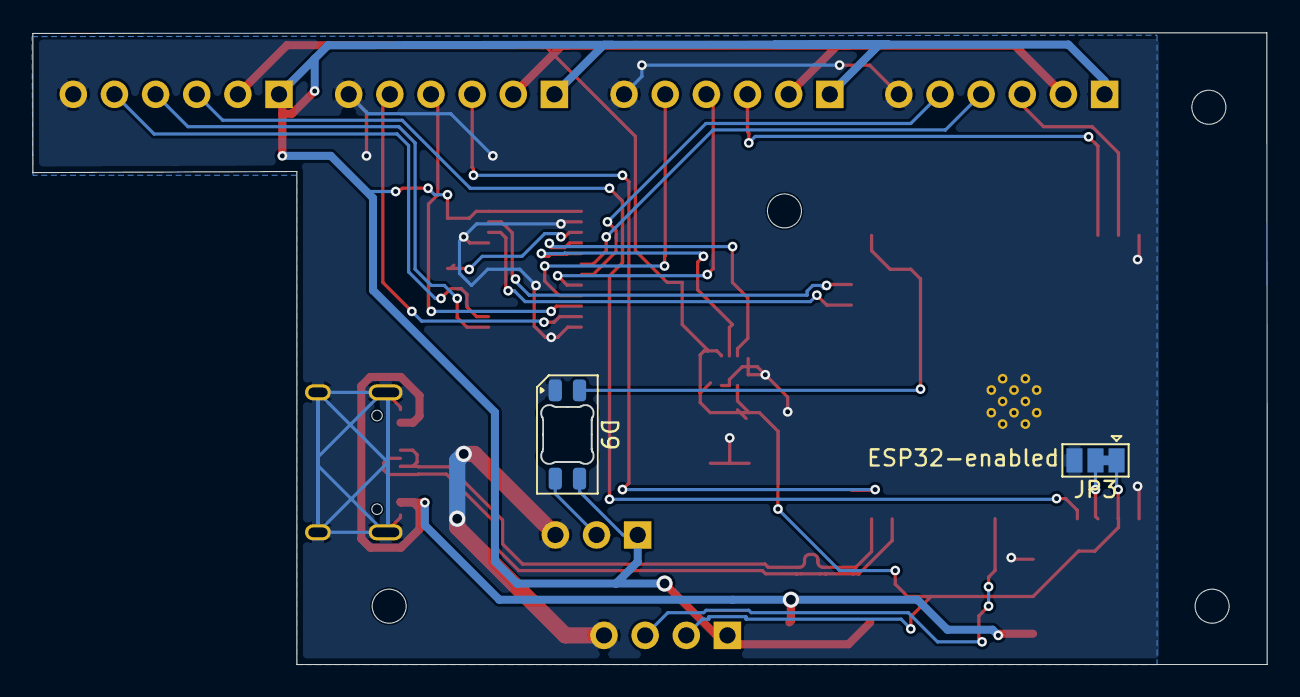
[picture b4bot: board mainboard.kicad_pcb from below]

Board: 2 copper layers, 76.2 x 39.0 mm, 19 parts (2 on the bottom side), 27 nets.

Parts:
C9, C10: 100nF; C_1206_3216Metric_Pad1.33x1.80mm_HandSolder
D9: SK6812MINI-E; LED_SK6812MINI-E_3.2x2.8mm_P1.5mm_ReverseMount
D15: D; D_SMA_Handsoldering
J1: USB_C_Receptacle_USB2.0_14P; USB_C_Receptacle_HRO_TYPE-C-31-M-12
J2: Conn_01x03; PinHeader_1x03_P2.54mm_Vertical
J12: Conn_01x04; PinSocket_1x04_P2.54mm_Vertical
J19, J20, J25, J29: Conn_01x06; PinHeader_1x06_P2.54mm_Vertical
JP3: ESP32-enabled; SolderJumper-3_P1.3mm_Bridged12_Pad1.0x1.5mm
R9, R10, R11: 10k; R_1206_3216Metric_Pad1.30x1.75mm_HandSolder
U1: LM1117MP-3.3; SOT-223-3_TabPin2
U3: LSM6DS3; LGA-14_3x2.5mm_P0.5mm_LayoutBorder3x4y
U4: ESP32-S3-WROOM-1
U16: TCA9548APWR; TSSOP-24_4.4x7.8mm_P0.65mm

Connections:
+3V3: C9.1, C10.1, J12.2, J19.2, J20.2, J25.2, J29.2, JP3.1 (A), R9.1, R10.1, U1.2 (VO), U3.5 (VDDIO), U3.8 (VDD), U3.12 (CS), U4.2 (3V3)
+5V: D9.3 (VDD), D15.1 (K), J2.1, J12.1, J19.1, J20.1, J25.1, J29.1, R11.1, U16.1 (A0), U16.24 (VCC)
BATT_SENSE: J12.3, U4.8 (IO15)
GND: C9.2, C10.2, D9.1 (VSS), J1.A1 (GND), J1.A12 (GND), J1.B1 (GND), J1.B12 (GND), J1.SH (SHIELD), J2.3, J12.4, J19.6, J20.6, J25.6, J29.6, JP3.3 (B), U1.1 (GND), U3.1 (SDO/SA0), U3.2 (SDX), U3.3 (SCX), U3.6 (GND), U3.7 (GND), U4.1 (GND), U4.40 (GND), U4.41 (GND), U16.2 (A1), U16.12 (GND), U16.21 (A2)
LED0: D9.2 (DIN), U4.27 (IO0)
LED1: J19.3, U4.39 (IO1)
LED2: J20.3, U4.38 (IO2)
LED3: J25.3, U4.15 (IO3)
LED4: J29.3, U4.4 (IO4)
unnamed: D9.4 (DOUT), J2.2
unnamed: D15.2 (A), J1.A4 (VBUS), J1.A9 (VBUS), J1.B4 (VBUS), J1.B9 (VBUS), U1.3 (VI)
unnamed: JP3.2 (C), U4.3 (EN)
unnamed: U4.24 (IO47), U16.22 (SCL)
unnamed: U4.25 (IO48), U16.23 (SDA)
unnamed: R11.2, U16.3 (~RESET)
SC0: R9.2, U3.13 (SCL), U16.5 (SC0)
SC1: J19.5, U16.7 (SC1)
SC2: J20.5, U16.9 (SC2)
SC3: J25.5, U16.11 (SC3)
SC4: J29.5, U16.14 (SC4)
SD0: R10.2, U3.14 (SDA), U16.4 (SD0)
SD1: J19.4, U16.6 (SD1)
SD2: J20.4, U16.8 (SD2)
SD3: J25.4, U16.10 (SD3)
SD4: J29.4, U16.13 (SD4)
USB_D+: J1.A6 (D+), J1.B6 (D+), U4.14 (USB_D+)
USB_D-: J1.A7 (D-), J1.B7 (D-), U4.13 (USB_D-)

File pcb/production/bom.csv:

Designator,Footprint,Quantity,Value,LCSC Part #
"C10, C9",1206,2,100nF,
D15,D_SMA_Handsoldering,1,D,
D9,LED_SK6812MINI-E_3.2x2.8mm_P1.5mm_ReverseMount,1,SK6812MINI-E,
J1,USB_C_Receptacle_HRO_TYPE-C-31-M-12,1,USB_C_Receptacle_USB2.0_14P,
J12,PinSocket_1x04_P2.54mm_Vertical,1,Conn_01x04,
"J19, J20, J25, J29",PinHeader_1x06_P2.54mm_Vertical,4,Conn_01x06,
J2,PinHeader_1x03_P2.54mm_Vertical,1,Conn_01x03,
"R10, R11, R9",1206,3,10k,
U1,SOT-223-3_TabPin2,1,LM1117MP-3.3,
U16,TSSOP-24_4.4x7.8mm_P0.65mm,1,TCA9548APWR,
U3,LGA-14_3x2.5mm_P0.5mm_LayoutBorder3x4y,1,LSM6DS3,
U4,ESP32-S3-WROOM-1,1,ESP32-S3-WROOM-1,

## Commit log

2026-05-24 init
2026-05-26 Organised files a bit
2026-05-26 Add production
2026-05-26 Added Zine
2026-05-26 Update production
2026-05-26 Updated BOM with links
2026-05-27 Add BOM.csv
2026-05-27 Add GitHub link for BOM CSV file
    Added link to open CSV file in GitHub for BOM.
2026-05-27 Add 'Why?' section to README
    Added a 'Why?' section explaining the inspiration behind the project.
2026-05-27 Added very basic firmware
2026-05-27 Remove excess BOMs
2026-06-08 Update README to remove center alignment
    Removed center tags from the OnShape link in README.
2026-06-08 Add assembly section to README
    Added assembly instructions to the README.
2026-06-08 Enhance assembly section with clearer steps and images
    Updated assembly instructions for clarity and added images.
2026-06-11 Add new image to final assembly section in README
2026-06-11 Create test
